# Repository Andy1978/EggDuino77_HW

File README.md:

https://www.pololu.com/product/1182
http://reprap.org/wiki/Pololu_stepper_driver_board

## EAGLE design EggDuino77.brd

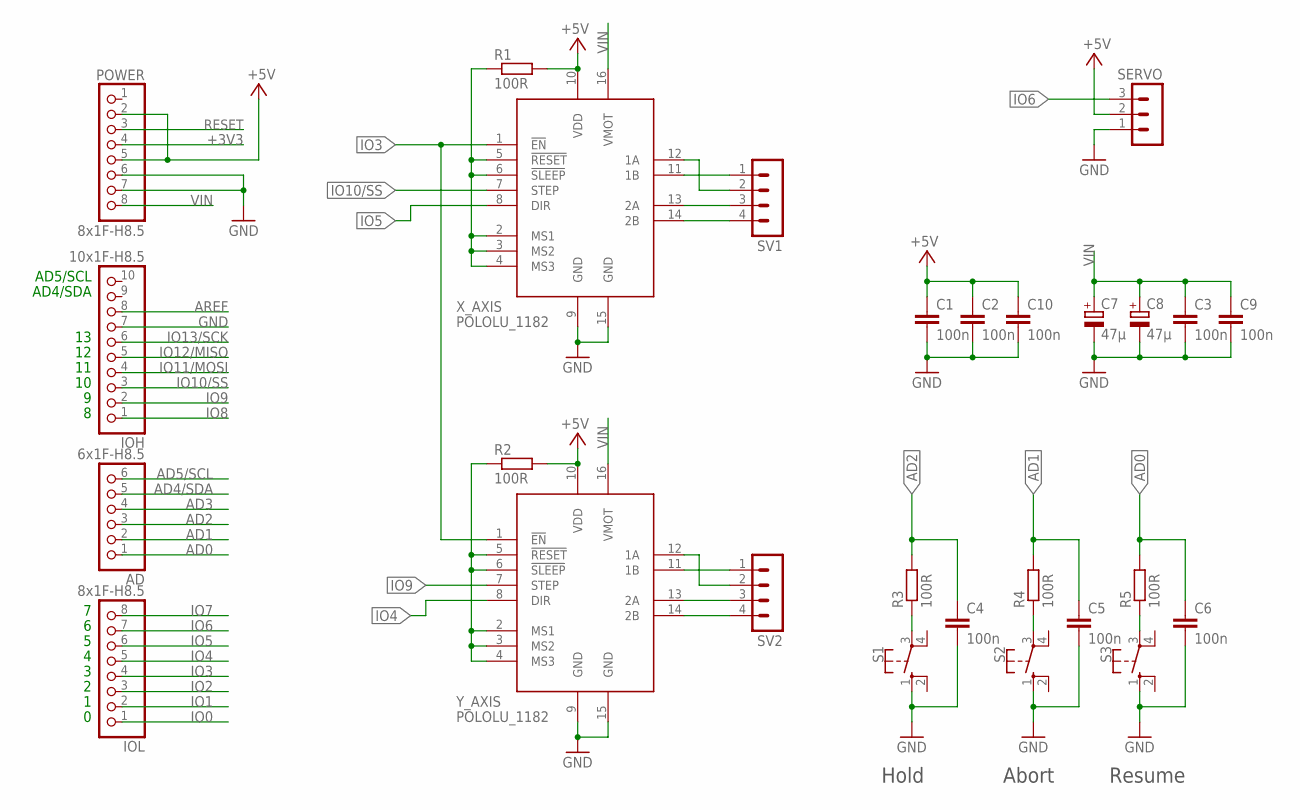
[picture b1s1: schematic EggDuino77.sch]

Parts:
AD: 6x1F-H8.5; 1X06
C1, C2, C3, C4, C5, C6, C9, C10: 100n; C0805
C7, C8: 47µ; E2,5-6E
IOH: 10x1F-H8.5; 1X10
IOL: 8x1F-H8.5; 1X08
POWER: 8x1F-H8.5; 1X08
R1, R2, R3, R4, R5: 100R; R0805
S1, S2, S3: 10-XX; B3F-10XX
SERVO: MA03-1
SV1, SV2: MA04-1
X_AXIS: POLOLU_1182; DIL16_WIDE
Y_AXIS: POLOLU_1182; DIL16_WIDE

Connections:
+3V3: POWER.4
+5V: C1.1, C2.1, C10.1, POWER.2, POWER.5, R1.2, R2.2, SERVO.2, X_AXIS.10 (VDD), Y_AXIS.10 (VDD)
AD0: AD.1, C6.1, R5.2
AD1: AD.2, C5.1, R4.2
AD2: AD.3, C4.1, R3.2
AD3: AD.4
AD4/SDA: AD.5
AD5/SCL: AD.6
AREF: IOH.8
GND: C1.2, C2.2, C3.2, C4.2, C5.2, C6.2, C7.-, C8.-, C9.2, C10.2, IOH.7, POWER.6, POWER.7, S1.1 (S), S2.1 (S), S3.1 (S), SERVO.1, X_AXIS.9 (GND), X_AXIS.15 (GND), Y_AXIS.9 (GND), Y_AXIS.15 (GND)
IO0: IOL.1
IO1: IOL.2
IO2: IOL.3
IO3: IOL.4, X_AXIS.1 (!EN), Y_AXIS.1 (!EN)
IO4: IOL.5, Y_AXIS.8 (DIR)
IO5: IOL.6, X_AXIS.8 (DIR)
IO6: IOL.7, SERVO.3
IO7: IOL.8
IO8: IOH.1
IO9: IOH.2, Y_AXIS.7 (STEP)
IO10/SS: IOH.3, X_AXIS.7 (STEP)
IO11/MOSI: IOH.4
IO12/MISO: IOH.5
IO13/SCK: IOH.6
unnamed: R2.1, Y_AXIS.2 (MS1), Y_AXIS.3 (MS2), Y_AXIS.4 (MS3), Y_AXIS.5 (!RESET), Y_AXIS.6 (!SLEEP)
unnamed: R1.1, X_AXIS.2 (MS1), X_AXIS.3 (MS2), X_AXIS.4 (MS3), X_AXIS.5 (!RESET), X_AXIS.6 (!SLEEP)
unnamed: SV1.4, X_AXIS.14 (2B)
unnamed: SV1.3, X_AXIS.13 (2A)
unnamed: SV1.2, X_AXIS.12 (1A)
unnamed: SV1.1, X_AXIS.11 (1B)
unnamed: SV2.1, Y_AXIS.11 (1B)
unnamed: SV2.4, Y_AXIS.14 (2B)
unnamed: SV2.3, Y_AXIS.13 (2A)
unnamed: SV2.2, Y_AXIS.12 (1A)
unnamed: R3.1, S1.3
unnamed: R4.1, S2.3
unnamed: R5.1, S3.3
RESET: POWER.3
VIN: C3.1, C7.+, C8.+, C9.1, POWER.8, X_AXIS.16 (VMOT), Y_AXIS.16 (VMOT)

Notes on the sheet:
AD4/SDA
AD5/SCL
Resume
Abort
Hold

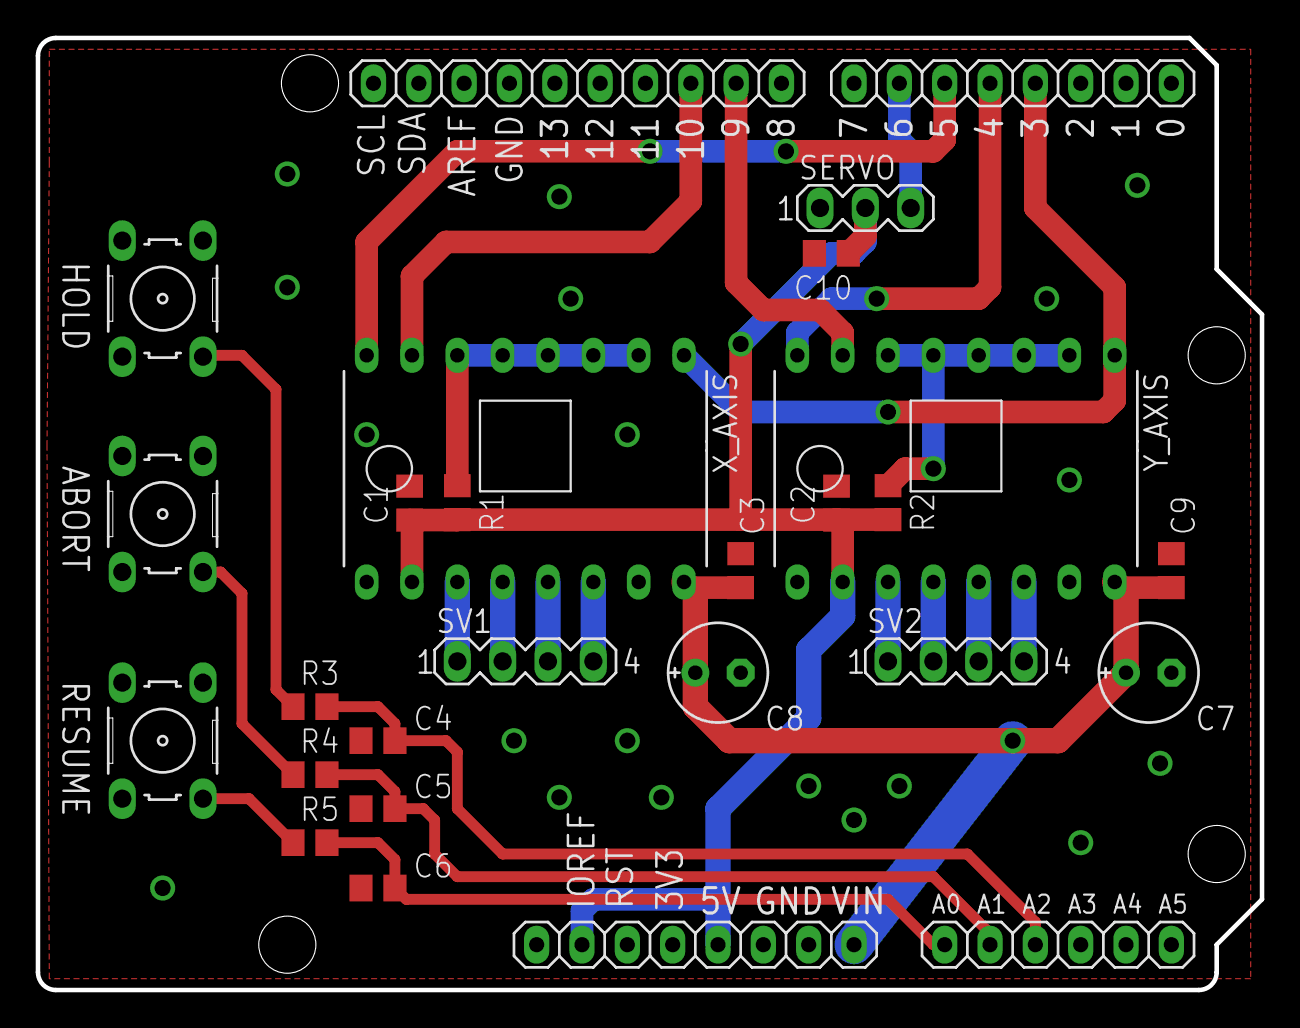
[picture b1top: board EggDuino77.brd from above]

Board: 2 copper layers, 68.6 x 53.3 mm, 27 parts (0 on the bottom side), 25 nets.

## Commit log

2018-03-06 Add first schematics and board
2018-03-06 Add GND vias
